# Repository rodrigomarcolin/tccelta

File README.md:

# tccelta
Repositório para o Trabalho de Conclusão de Curso do Bacharelado em Engenharia de Computação da Escola Politécnica da Universidade de São Paulo.

# Sumário

1. [Introdução](#introdução)
1. [Arquitetura](#arquitetura)
1. [Funcionamento Típico](#funcionamento-típico)
1. [Segurança](#segurança)

# Introdução [↩](#sumário)

> Obs: recomenda-se a leitura dos texto auxiliar [CAN e OBD-II](docs/can-e-obd2.md).

Este repositório contém um firmware para um Dongle OBD-II baseado em ESP-32 na pasta `esp32-firmware/`. Ele utiliza o [PlatformIO](https://platformio.org/) para gerenciar as dependências e o build e o upload do firmware.

Com o PlatformIO devidamente instalado e configurado em seu VSCode, conecte o ESP32 ao seu computador e abra a pasta esp32-firmware com o VSCode. Após isto, é possível abrir a interface da extensão e escolher qual dos perfis, configurados no arquivo `esp32-firmware/platformio.ini`, deve ser utilizado para Build e Upload. Cada perfil irá definir variáveis de ambiente, que são utilizadas em macros no código, as quais decidem quais implementações instanciar.

A pasta `simulador/` contém um simulador de ECU baseado no projeto [ECUSim](https://github.com/sugiuraii/ECUSim) (licença MIT, ver `simulador/LICENSE`), adaptado neste TCC para simular DTCs (Diagnostic Trouble Codes) além dos PIDs originais. Mais detalhes sobre a origem e as adaptações estão em `simulador/README.md`.

# Arquitetura [↩](#sumário)

O firmware está estruturado em camadas, conforme a seguinte imagem:

Cada camada na imagem concretiza-se como uma pasta dentro de esp32-firmware/src. Cada pasta contém um arquivo .h com a interface da camada, e pode possuir uma ou mais implementações. Como cada camada comunica-se somente com a camada inferior através de sua interface padronizada, é possível trocar a implementação de uma dada camada sem maiores impactos no código. Por exemplo, para fins de desenvolvimento da comunicação Esp32 - Companion App, pode ser um estorvo ter que fazer todo o setup envolvendo os componentes físicos do dongle que interagem com o CAN. Por isso, é possível instanciar a camada OBD-II mockada, que retorna respostas construídas e dispensa a necessidade de componentes CAN. 

Abaixo, é possível observar mais detalhes sobre as responsabilidades de cada camada:

# Funcionamento Típico [↩](#sumário)
O funcionamento típico é o seguinte: 

1. No Setup, as características BLE são configuradas; as implementações de cada camada, escolhidas via variáveis de ambientes no perfil PlatformIO escolhido, são instanciadas; os métodos de inicialização relevantes são executados; e o dispositivo começa a se anunciar.
2. Um cliente BLE conecta-se ao dispositivo.
3. Um cliente BLE escreve um comando ELM327 na característica RX do BLE.
4. O callback `onWrite` da classe `BLEConnectivity` executa, e como consequência o comando ELM327 recebido é colocado na fila à qual a tarefa `ELM327Task` escuta.
5. A tarefa `ELM327Task` reage à entrada do comando na fila, e inicia o seu processamento chamando o método `process` da classe ELM327.
6. Consequentemente, pode ser gerada uma requisição à camada OBD-II. Se a implementação escolhida for a mockada, alguma lógica executará no sentido de gerar uma resposta coerente. Se a implementação escolhida for a real, será construída uma requisição OBD-II (que, conforme a [documentação CAN e OBD-II](docs/can-e-obd2.md), viverá no campo DATA da mensagem CAN). Então, será repassada para a camada CAN, que interagirá com o componente CAN relevante para colocar a requisição no barramento, esperar uma resposta, e retornar seu conteúdo.
7. A resposta OBD-II será processada e colocada no TX do BLE.
8. O cliente será notificado e poderá fazer o que bem entender com a resposta do DONGLE ao seu comando ELM-327 =)

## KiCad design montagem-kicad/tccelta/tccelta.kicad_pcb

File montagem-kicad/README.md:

# Dongle OBD-II (TCC) - placa de face simples feita em casa

Projeto KiCad 10 em `tccelta/`. A placa liga o cabo OBD-II (12 V + CAN) a um ESP32 e a um transceptor CAN
SN65HVD230 (placa Waveshare "SN65HVD230 CAN Board"), com um buck LM2596 para gerar os 5 V. Os **módulos não são
soldados**: encaixam em soquetes fêmea (barras de pinos fêmea de 2,54 mm). Só os soquetes, os bornes, o F1, o D1,
o C1, o R1 e as barras macho J3 e JP1 são soldados.

Entrada de 12 V, na ordem: borne -> **F1** (fusível rearmável PTC 0,4 A) -> **D1** (1N5819, inversão de polaridade)
-> **C1** (100 uF) -> LM2596.

Terminação CAN de 120 ohms **selecionável por jumper**: o resistor **R1** (120 ohms) fica ligado entre CAN_L e o pino
**JP1**; o outro pino do JP1 vai ao CAN_H. Com o jumper colocado (bancada, simulador) o dongle termina o barramento;
sem o jumper (carro) não termina, porque o carro já tem os seus dois resistores.

**Versão 2 (transceptor deitado sob o ESP32, placa 54,1 x 63,5 mm, sem J3 nem fios): veja [V2_TRANSCEPTOR_SOB_ESP32.md](V2_TRANSCEPTOR_SOB_ESP32.md) e a pasta [`tccelta_v2/`](tccelta_v2/).**

Tamanho da placa: **54,1 x 72,4 mm** (cantos arredondados de 2 mm). Cobre só em B.Cu, **sem vias, sem jumpers**.

O procedimento completo de fabricação e montagem está em [PASSO_A_PASSO.md](PASSO_A_PASSO.md), e a lista de
ferramentas e materiais em [MATERIAIS.md](MATERIAIS.md). A função e a posição de cada elemento estão explicadas em
[ESCOLHAS_DO_PROJETO.md](ESCOLHAS_DO_PROJETO.md).

## Arquivos

| Arquivo | O que é |
|---|---|
| `tccelta/tccelta.kicad_sch` | esquemático (A4, 5 blocos) |
| `tccelta/tccelta.kicad_pcb` | PCB roteada, plano de GND em B.Cu |
| `tccelta/tccelta.kicad_sym`, `tccelta/tccelta.pretty/` | símbolos e footprints próprios (ESP32, LM2596, SN65 em pé) |
| `tccelta/scripts/gerar_placa.py` | gera tudo do zero (símbolos, footprints, esquemático, PCB, exportações) |
| `tccelta/fabricacao/` | PDFs 1:1, furação, renders, esquemático em PDF/SVG |

## BOM (lista de materiais)

| Qtd | Item | Observação |
|---|---|---|
| 1 | DOIT ESP32 DevKit V1, 30 pinos (2 x 15) | encaixa em 2 soquetes fêmea de 15 pinos |
| 1 | Módulo buck LM2596 (placa azul, 43 x 21 mm) | você solda 4 pinos macho nos furos do módulo |
| 1 | Módulo "SN65HVD230 CAN Board" (Waveshare, ~37 x 14 mm) | montado **em pé**; **remover sempre** o resistor SMD de 120 ohms dele (marcado "121"): a terminação passa a ser o R1 + JP1 |
| 1 | Barra de pinos **fêmea** 1x15, 2,54 mm | soquete do ESP32, fileira de cima (EN na ponta da antena) |
| 1 | Barra de pinos **fêmea** 1x14, 2,54 mm | soquete do ESP32, fileira de baixo: **sem contato na posição do D23** (ponta da antena); alinhe a barra ao pino D22 |
| 1 | Barra de pinos **fêmea** 1x4, 2,54 mm, vertical comum | soquete do transceptor (recebe a barra de 4 pinos de 90 graus do módulo, como vem de fábrica) |
| 4 | Soquete **fêmea** de 1 pino (ou 4 pinos cortados de uma barra fêmea) | soquete do LM2596 |
| 4 | Pino macho 2,54 mm | soldar nos 4 furos do LM2596 |
| 1 | Barra de pinos **macho** 1x2, 2,54 mm, vertical | J3 "CAN p/ módulo" (H = CAN_H, L = CAN_L) |
| 2 | Jumper dupont fêmea, até 10 cm, trançados entre si | liga J3 aos pinos CANH/CANL do módulo (ou ao borne dele) |
| 1 | R1: resistor de filme metálico 120 ohms, 1/4 W, 1 % (axial, montado em pé) | terminação CAN (dissipa ~33 mW) |
| 1 | Barra de pinos **macho** 1x2, 2,54 mm, vertical | JP1 "TERM 120R" (sai da mesma barra 1x40 do J3) |
| 1 | Jumper de encaixe (shunt) 2,54 mm | fecha o JP1: colocado na bancada, retirado no carro |
| 1 | Barra de pinos **macho** 1x2, 2,54 mm, vertical | J5 "PAIR" (botão de pareamento externo: pino 1 = GPIO19, pino 2 = GND) |
| 1 | Botão táctil (ex.: 12x12 mm com capinha) com 2 fios dupont fêmea soldados em pernas de lados opostos | liga ao J5; segurar 5 s com o dongle ligado abre a janela de pareamento (sem caixa: botão solto na ponta dos fios) |
| 1 | Borne de parafuso 2 vias, passo 5,08 mm (Phoenix MKDS 1,5/2) | J1: 12 V e GND |
| 1 | Borne de parafuso 3 vias, passo 5,08 mm (MKDS 1,5/3) | J2: GND, CAN_H, CAN_L; encaixa no J1 formando 5 vias |
| 1 | F1: fusível rearmável PTC radial, **0,4 A** de manutenção (desarma a 0,8 A), **60 V ou mais** (RXEF040, MF-R040 ou similar), terminais a 5,1 mm | abre num curto na placa e volta sozinho depois de esfriar. Não use os de 16 V. Se desarmar à toa no calor, troque pelo RXEF050 (0,5 A), no mesmo lugar |
| 1 | D1: diodo Schottky 1N5819 (DO-41) | proteção contra inversão de polaridade |
| 1 | C1: capacitor eletrolítico 100 uF / 25 V (radial, D 6,3 mm, passo 2,5 mm) | |
| 3 | Parafuso M3 + porca (ou espaçador) | furos de fixação H1, H2, H3 |
| - | Fenolite de face simples, ~60 x 76 mm | |

Total de pinos de soquete e barra a soldar: 29 (ESP32) + 4 (transceptor) + 4 (LM2596) + 2 (J3) + 2 (JP1) + 2 (J5) = 43,
mais as 2 pernas do R1.

Sobre o módulo Waveshare: a barra de 4 pinos de 90 graus que ele já traz é justamente o que permite a montagem em
pé. Os pinos saem paralelos à placa do módulo e, encaixados apontando para baixo num soquete fêmea vertical, o módulo
fica **perpendicular à PCB**. Não é preciso dobrar nem trocar a barra. O módulo é montado com o **lado dos componentes
(e o borne de parafuso CAN) voltado para DENTRO da placa (norte)**; olhando de dentro da placa para a borda de baixo,
os pinos ficam, da esquerda para a direita: 3V3, GND, CAN RX, CAN TX (na PCB, de oeste para leste: CAN_TX, CAN_RX,
GND, 3V3, como mostra a serigrafia). O borne do módulo fica a cerca de 27-37 mm de altura, avançando ~10 mm para dentro
da placa, sem tocar nada.

## Medidas a conferir (paquímetro) e como regenerar

As medidas dos módulos são estimativas. Confira no topo de `tccelta/scripts/gerar_placa.py` (constantes marcadas
`CONFERIR COM PAQUIMETRO`) e ajuste se for diferente:

| Constante | Valor atual |
|---|---|
| `ESP32_PINOS_POR_FILEIRA` | 15 |
| `ESP32_ESPACAMENTO_FILEIRAS` | 22,86 mm (0,9", típico do DOIT V1; ainda não medido) |
| `ESP32_COMPRIMENTO` / `ESP32_LARGURA` | 51,5 / 28,3 mm |
| `ESP32_ANTENA_AVANCO` (além do pino 1) | 8,0 mm |
| `ESP32_ANTENA_INICIO_APOS_PINO1` | 1,5 mm (nenhum cobre além de pino 1 + 1,0 mm; `ESP32_KEEPOUT_INICIO`) |
| `LM2596_COMPRIMENTO` / `LM2596_LARGURA` | 43,0 / 21,0 mm |
| `LM2596_FURO_BORDA_CURTA` | 2,0 mm |
| `LM2596_FUROS_LARGURA` / `LM2596_FUROS_COMPRIMENTO` | 17,0 / 39,0 mm |
| `SN65_MODULO_LARGURA` / `SN65_MODULO_ALTURA` | 14,0 / 37,0 mm |
| `SN65_MODULO_ESPESSURA` | 2,0 mm |
| `SN65_BORNE_SALIENCIA` / `SN65_BORNE_LARGURA` | 10,0 / 10,0 mm |
| `SN65_ORDEM_PINOS` | CAN_TX, CAN_RX, GND, 3V3 (oeste -> leste na PCB) |

Duas suposições que só o módulo físico responde (use o teste em papel abaixo):

- **LM2596**: IN+ e OUT+ estão na mesma lateral longa (a de baixo, voltada ao ESP32) e IN-/OUT- na outra,
  com IN à esquerda e OUT à direita.
- **SN65HVD230 Waveshare**: olhando para o lado dos componentes (o borne CAN vem na sua direção) com a barra de
  pinos embaixo, a ordem da esquerda para a direita é 3V3, GND, CAN RX, CAN TX. Na PCB o lado dos componentes e
  o borne ficam voltados **para dentro** da placa (norte). Outra ordem exige rever o roteamento (o script avisa).

Para regenerar tudo depois de mudar uma constante (use o Python do KiCad):

```
C:/Users/davif/AppData/Local/Programs/KiCad/10.0/bin/python.exe montagem-kicad/tccelta/scripts/gerar_placa.py
```

O script reescreve símbolos, footprints, esquemático, PCB e `fabricacao/`, e imprime o resultado do ERC, do DRC
(com paridade esquemático x PCB) e a conferência de escala 1:1 dos PDFs.

## Teste em papel 1:1

1. Imprima `tccelta/fabricacao/teste_papel_1x1.pdf` em **100 % (tamanho real, sem "ajustar à página")**.
2. Recorte e espete os pinos dos módulos nos furos do papel: ESP32, LM2596 e soquete do transceptor devem
   encaixar sem folga. O desenho do transceptor mostra a linha fina do módulo em pé e a seta "COMPONENTES E BORNE PARA DENTRO".
3. Meça o papel impresso com o paquímetro: a placa deve ter 54,2 x 72,5 mm. Se não, a impressora está escalando.
4. Se algo não encaixar, ajuste as constantes, rode o script de novo e repita.

## Impressão e transferência (toner)

1. Imprima `tccelta/fabricacao/cobre_B_Cu_toner.pdf` em impressora **laser**, em papel glossy/de transferência,
   **100 % de escala, sem espelhar**. O arquivo já está na orientação certa: a transferência inverte a imagem
   e o texto de cobre fica legível na placa pronta, vista pelo lado do cobre.
2. Limpe o fenolite com palha de aço fina e álcool isopropílico. Alinhe o papel com o toner voltado para o cobre.
3. Transfira com ferro quente (algumas passadas firmes) ou laminadora. Deixe esfriar e solte o papel na água.
4. Retoque falhas com caneta de retroprojetor ou esmalte.

Cada pad tem no centro um ponto branco de 0,35 mm, sem toner: depois da corrosão ele vira um pontinho sem cobre que
marca o centro do furo e serve de guia para o punção. Os furos M3 não têm pad: o centro deles é o centro do círculo
sem cobre que o plano de GND deixa em volta.

## Corrosão e furação

1. Corroa em percloreto de ferro morno (cerca de 40 C), agitando. Retire quando todo o cobre exposto sumir.
2. Lave, remova o toner com acetona e passe palha de aço fina.
3. Fure da face do cobre:
   - **1,0 mm**: soquetes do ESP32 (29), do transceptor (4), do LM2596 (4), J3 (2), JP1 (2), J5 (2), R1 (2) e F1 (2): 47 furos.
   - **1,0 a 1,1 mm** para os pads do D1 (2) e **0,8 a 1,0 mm** para o C1 (2): alargue se as pernas não entrarem.
   - **1,3 mm**: bornes J1 e J2 (5 furos).
   - **3,2 mm**: furos de fixação M3 (3).
   Total: 57 furos. Veja `tccelta/fabricacao/furacao.txt` para a lista completa (e `tccelta.drl`, formato Excellon).

A serigrafia (referências e rótulos dos pinos) está em `serigrafia_F_Silk.pdf` como guia de montagem, e em
`serigrafia_F_Silk_espelhada.pdf` para quem quiser transferi-la por toner no lado dos componentes (veja
[PASSO_A_PASSO_SERIGRAFIA.md](PASSO_A_PASSO_SERIGRAFIA.md)).

## Montagem

1. Solde **somente**: as barras fêmea (ESP32 1x15 + 1x14, transceptor), os 4 soquetes do LM2596, os bornes J1 e J2, a barra
   macho J3, o R1, a barra macho JP1, o F1, o D1 e o C1. Componentes por cima; solda e cobre embaixo.
   - F1: não tem polaridade. Fica no canto de baixo à esquerda, entre o borne e o D1. Solde com o disco **uns 3 a 4 mm
     acima da placa** (as dobras dos terminais já seguram nessa altura), para a cabeça do parafuso do furo H2 passar
     por baixo da borda dele.
   - R1 (120 ohms): montado **em pé**, com o corpo sobre o pad de cima (ao lado do JP1) e a perna dobrada para o pad de baixo.
     Não tem polaridade.
   - JP1: barra macho 1x2 vertical, ao lado do R1. O jumper de encaixe vai sobre os dois pinos.
   - D1: **faixa (catodo) voltada para cima** na placa (pad de cima), anodo para baixo, ligado ao F1.
   - C1: fica em cima, à esquerda, ao lado do ESP32 e logo abaixo do IN+ do LM2596. Perna longa (+) no pad da
     esquerda, marcada com "+" no desenho.
   - Encaixe o J2 ao lado do J1 (borne de 5 vias): `+12V, GND, GND, CAN_H, CAN_L`. A entrada dos fios
     fica voltada para a borda de baixo da placa.
2. Solde os 4 pinos macho nos furos do LM2596.
3. Encaixe o LM2596 e **ajuste a saída para 5,0 V com o multímetro ANTES de encaixar o ESP32** (ligue 12 V no borne).
4. Desligue e encaixe o ESP32 (antena para a direita, para fora da placa; USB do lado esquerdo; o pino EN fica na
   ponta da antena e o VIN na ponta do USB).
5. Encaixe o transceptor **em pé** no soquete 1x4, com os pinos de 90 graus apontando para baixo, **com o lado dos
   componentes e o borne voltados para DENTRO da placa** (siga a seta no desenho). Se entrar ao contrário,
   3V3/GND/CAN ficam trocados.
6. Ligue dois fios dupont **trançados** (até 10 cm) de J3 (H = CAN_H, L = CAN_L) aos pinos CANH/CANL do módulo
   (ou ao borne de parafuso dele).
7. **Remova o resistor SMD de 120 ohms do módulo Waveshare** (marcado "121", perto do borne CAN) antes de usá-lo.
   Veja o passo a passo.
8. Cabo OBD-II: pino 16 = +12 V, pinos 4 e 5 = GND, pino 6 = CAN_H, pino 14 = CAN_L, nos 5 vias do borne.

O firmware usa TX = GPIO21 e RX = GPIO22 (pinos D21 e D22 do ESP32 DevKit V1) e lê o botão de pareamento (J5) no GPIO19 (D19), ativo em nível baixo (o BOOT/GPIO0 do DevKit não sai no soquete). O VIN do ESP32 recebe os 5 V do buck.

## Avisos

- **Não ligue o USB do ESP32 ao mesmo tempo que os 12 V**, a menos que a placa do ESP32 tenha diodo no VBUS.
  Os 5 V do buck entram pelo pino VIN, que no DOIT V1 é o mesmo nó dos 5 V do USB.
- **O resistor SMD de 120 ohms do módulo SN65 deve ser removido sempre, na montagem.** A terminação do dongle é o
  JP1: **com jumper na bancada** (simulador), **sem jumper no carro**, onde o barramento já tem terminação nas duas
  pontas. Dois resistores no dongle (o do módulo e o R1) dariam 40 ohms no total e sobrecarregariam o barramento.
- **Só encaixe o transceptor na orientação certa** (lado dos componentes e borne para dentro): o soquete 1x4 não tem chave
  e invertê-lo liga o 3V3 no pino de CAN TX.
- O transceptor em pé chega a ~37 mm acima da placa; deixe a caixa/uso compatível com essa altura. O borne dele
  avança ~10 mm para dentro da placa (sobre a área livre entre o transceptor e o ESP32, no alto).
- A antena do ESP32 avança além da borda direita da placa (a borda fica 2,0 mm depois do centro do pino 1) e **não
  há cobre além de pino 1 + 1,0 mm**: nem trilha, nem plano de GND. Há uma área proibida de cobre sob a antena.
- O contato do D23 (ponta da antena, fileira de baixo) não existe na PCB: o D23 não é usado e, sem esse pad, o
  plano de GND passa entre o D22 e a borda e liga o GND do transceptor ao restante, sem bolsões. O pino D23 do
  ESP32 fica sem contato (use a barra 1x14 na fileira de baixo).
- Dois pads de GND (GND do transceptor e C1 -) usam conexão sólida ao plano em vez de alívio térmico: só há espaço
  para um raio no primeiro e o C1 é o capacitor de entrada. Os demais mantêm alívio térmico de 0,8 mm.
- C1 fica colado no IN+ do buck (canto de cima à esquerda, ao lado do ESP32, fora do contorno dele e do módulo): o
  pino + está a ~7,5 mm de trilha do IN+. A trilha de +12 V_PROT sobe do D1 até o + do C1 e dali vai ao IN+ (ordem
  D1 -> C1 -> IN+). A placa não cresceu.
- **F1 (PTC)** é o primeiro componente depois do borne, então protege tudo o que vem depois (D1, C1, buck, ESP32,
  transceptor) contra curto. O consumo normal é de ~0,15 A em 12 V; o PTC de 0,4 A garante abrir a 0,8 A (abaixo do
  1 A do D1) e, num carro quente (~60 °C), ainda segura uns 0,28 A. O risco é desarmar à toa em calor forte; veja
  [ESCOLHAS_DO_PROJETO.md](ESCOLHAS_DO_PROJETO.md#riscos-do-fusível-de-04-a). Quando abre, esquenta (é assim que ele corta) e volta sozinho alguns minutos
  depois de desligar. Ele não protege o cabo entre o conector OBD-II e a placa: esse trecho continua só com o
  fusível do próprio carro.
- O furo de fixação H2 fica colado ao F1: a cabeça de um parafuso M3 comum (5,5 mm) avança ~0,5 mm sob a borda do
  disco do PTC visto de cima. Por isso o F1 vai soldado um pouco alto (ver Montagem).

## Validação (resultado atual)

ERC: 0 violações. DRC com paridade esquemático x PCB: 0 violações, 0 itens desconectados, 0 problemas de paridade
(igual à linha de base anterior ao R1/JP1, sem erro nem aviso novo). Netlist conferida contra o modelo (inclui a rede
`TERM`). Escala 1:1 dos PDFs conferida; tamanho da placa inalterado (54,1 x 72,4 mm).

Medidas esperadas com o multímetro (tudo desligado, resistor do módulo removido): só o dongle com JP1 e sem nada
ligado = 120 ohms entre CAN_H e CAN_L; dongle + simulador com JP1 = ~60 ohms; no carro, sem JP1 = ~60 ohms (o do carro).

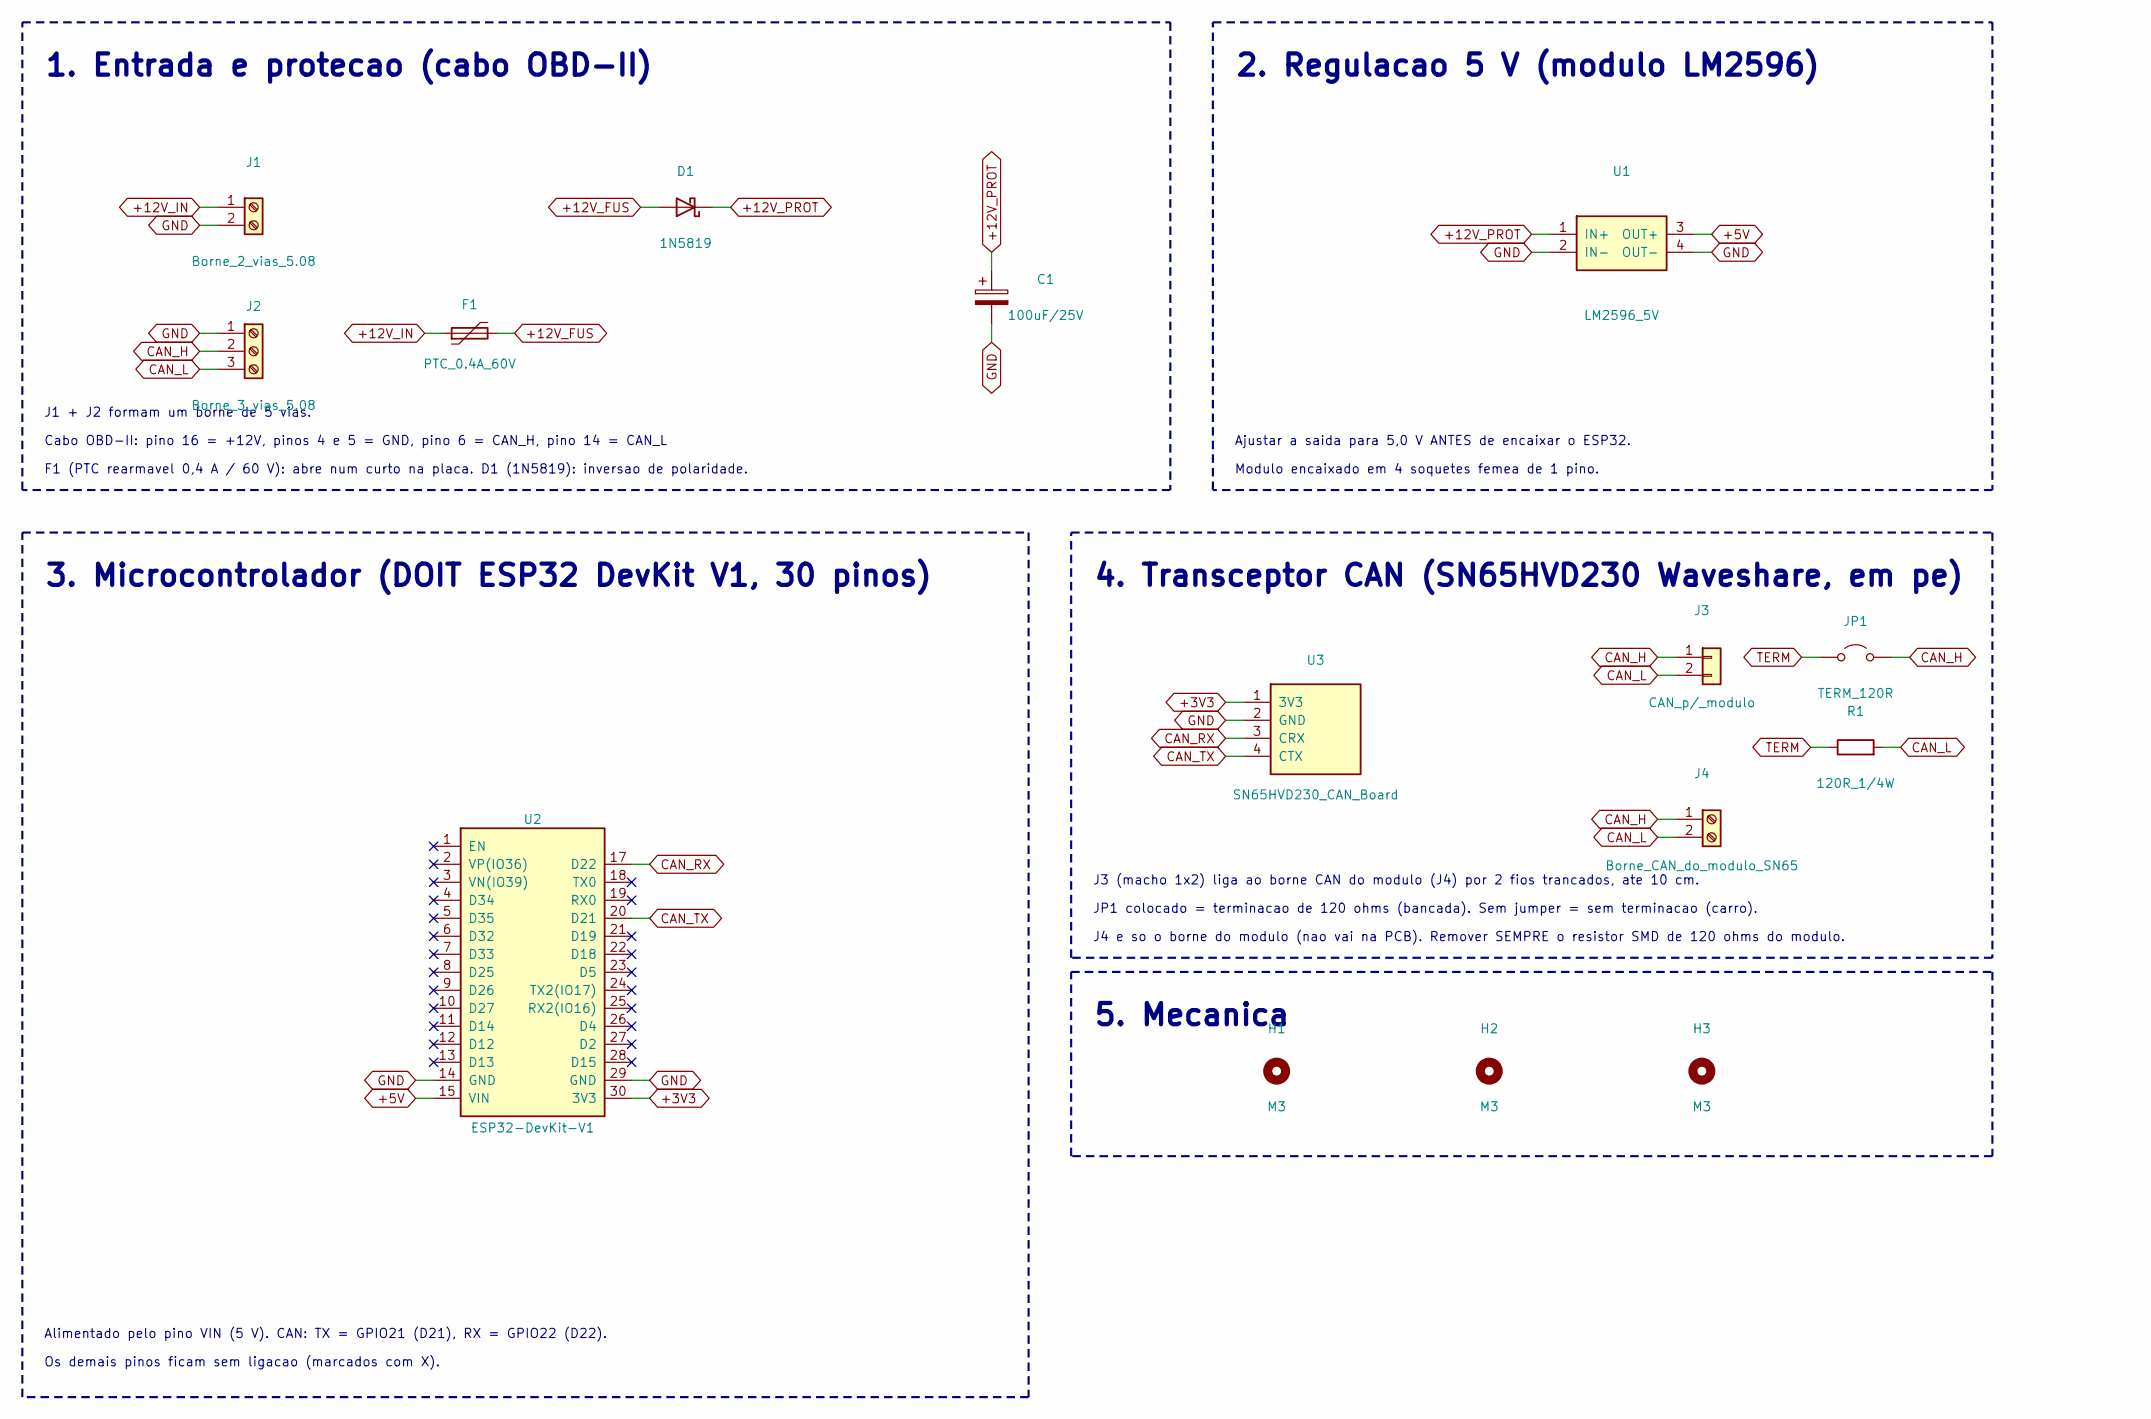
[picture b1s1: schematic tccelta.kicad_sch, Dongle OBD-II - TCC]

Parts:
C1: 100uF/25V; CP_Radial_D6.3mm_P2.50mm
D1: 1N5819; D_DO-41_SOD81_P7.62mm_Horizontal
F1: PTC_0.4A_60V; PTC_Radial_P5.08_Vertical
H1, H2, H3: M3; MountingHole_3.2mm_M3
J1: Borne_2_vias_5.08; TerminalBlock_Phoenix_MKDS-1,5-2-5.08_1x02_P5.08mm_Horizont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
J2: Borne_3_vias_5.08; TerminalBlock_Phoenix_MKDS-1,5-3-5.08_1x03_P5.08mm_Horizont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
J3: CAN_p/_modulo; PinHeader_1x02_P2.54mm_Vertical
J4: Borne_CAN_do_modulo_SN65
JP1: TERM_120R; PinHeader_1x02_P2.54mm_Vertical
R1: 120R_1/4W; R_Axial_DIN0207_L6.3mm_D2.5mm_P2.54mm_Vertical
U1: LM2596_5V; LM2596_Modulo_Soquete
U2: ESP32-DevKit-V1; ESP32_DevKitV1_30_Soquete
U3: SN65HVD230_CAN_Board; SN65HVD230_Waveshare_EmPe

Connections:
+3V3: U2.30 (3V3), U3.1 (3V3)
+5V: U1.3 (OUT+), U2.15 (VIN)
+12V_FUS: D1.2 (A), F1.2
+12V_IN: F1.1, J1.1
+12V_PROT: C1.1, D1.1 (K), U1.1 (IN+)
CAN_H: J2.2, J3.1, J4.1, JP1.2 (B)
CAN_L: J2.3, J3.2, J4.2, R1.2
CAN_RX: U2.17 (D22), U3.3 (CRX)
CAN_TX: U2.20 (D21), U3.4 (CTX)
GND: C1.2, J1.2, J2.1, U1.2 (IN-), U1.4 (OUT-), U2.14 (GND), U2.29 (GND), U3.2 (GND); also elsewhere on the board
PAIR_BTN: U2.21 (D19); also elsewhere on the board
TERM: JP1.1 (A), R1.1

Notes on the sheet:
1. Entrada e protecao (cabo OBD-II)
Cabo OBD-II: pino 16 = +12V, pinos 4 e 5 = GND, pino 6 = CAN_H, pino 14 = CAN_L
F1 (PTC rearmavel 0,4 A / 60 V): abre num curto na placa. D1 (1N5819): inversao de polaridade.
J1 + J2 formam um borne de 5 vias.
2. Regulacao 5 V (modulo LM2596)
Ajustar a saida para 5,0 V ANTES de encaixar o ESP32.
Modulo encaixado em 4 soquetes femea de 1 pino.
3. Microcontrolador (DOIT ESP32 DevKit V1, 30 pinos)
Alimentado pelo pino VIN (5 V). CAN: TX = GPIO21 (D21), RX = GPIO22 (D22).
Os demais pinos ficam sem ligacao (marcados com X).
4. Transceptor CAN (SN65HVD230 Waveshare, em pe)
J3 (macho 1x2) liga ao borne CAN do modulo (J4) por 2 fios trancados, ate 10 cm.
J4 e so o borne do modulo (nao vai na PCB). Remover SEMPRE o resistor SMD de 120 ohms do modulo.
JP1 colocado = terminacao de 120 ohms (bancada). Sem jumper = sem terminacao (carro).
5. Mecanica

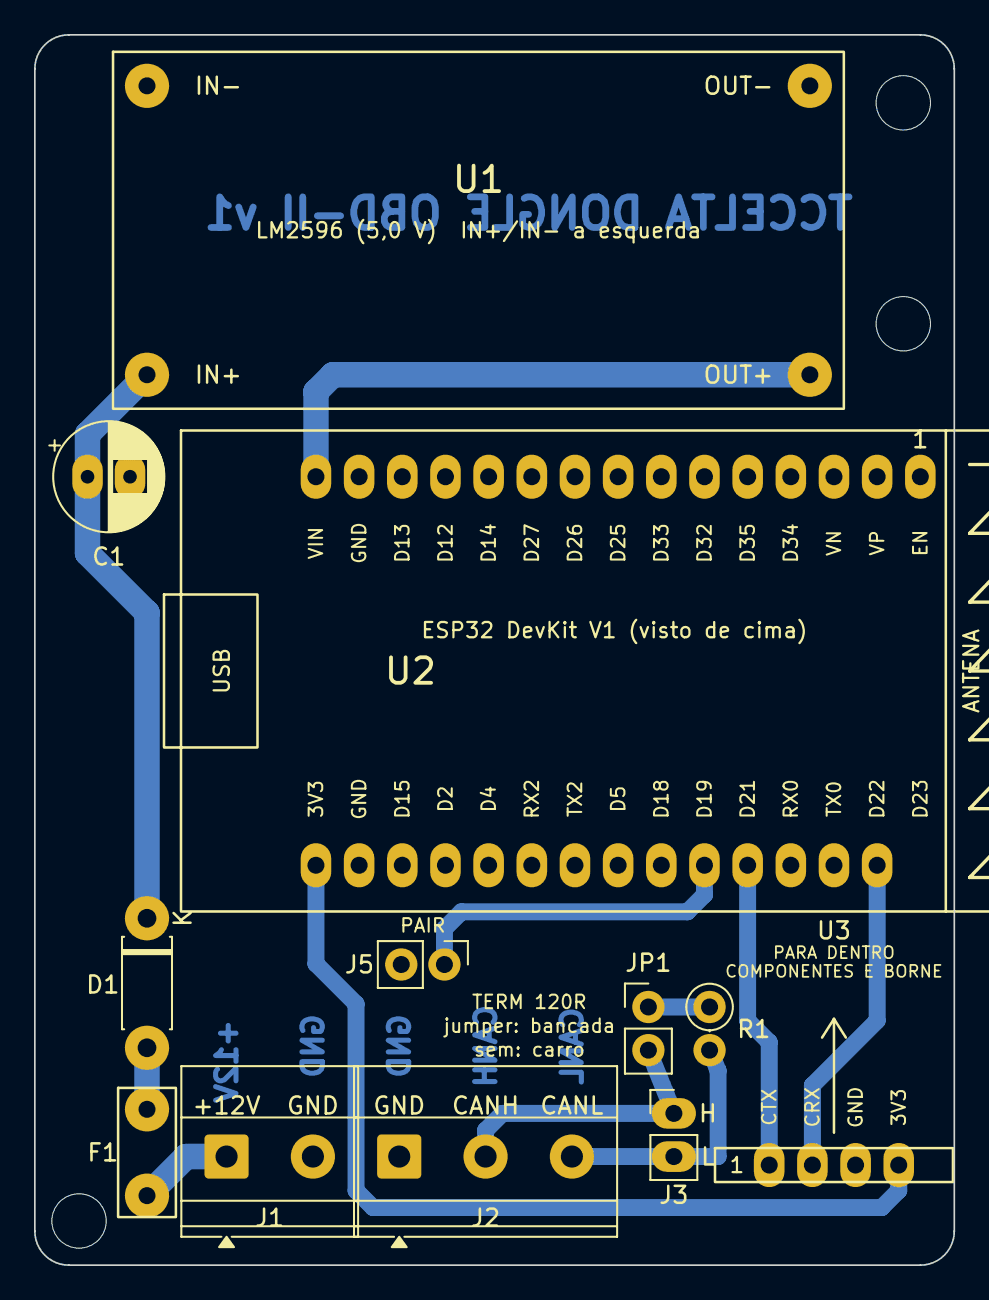
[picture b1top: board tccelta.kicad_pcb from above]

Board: 2 copper layers, 54.1 x 72.4 mm, 15 parts (0 on the bottom side), 12 nets.

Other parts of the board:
J5: BTN_PAREAMENTO; PinHeader_1x02_P2.54mm_Vertical

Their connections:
GND: J5.2; also elsewhere on the board
PAIR_BTN: J5.1; also elsewhere on the board
